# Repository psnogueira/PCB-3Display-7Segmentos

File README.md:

# PCB-3Display-7Segmentos
Projeto esquemático e PCB de um circuito controlado por Arduino de 3 displays de 7 segmentos de um contador de 0 a 999.

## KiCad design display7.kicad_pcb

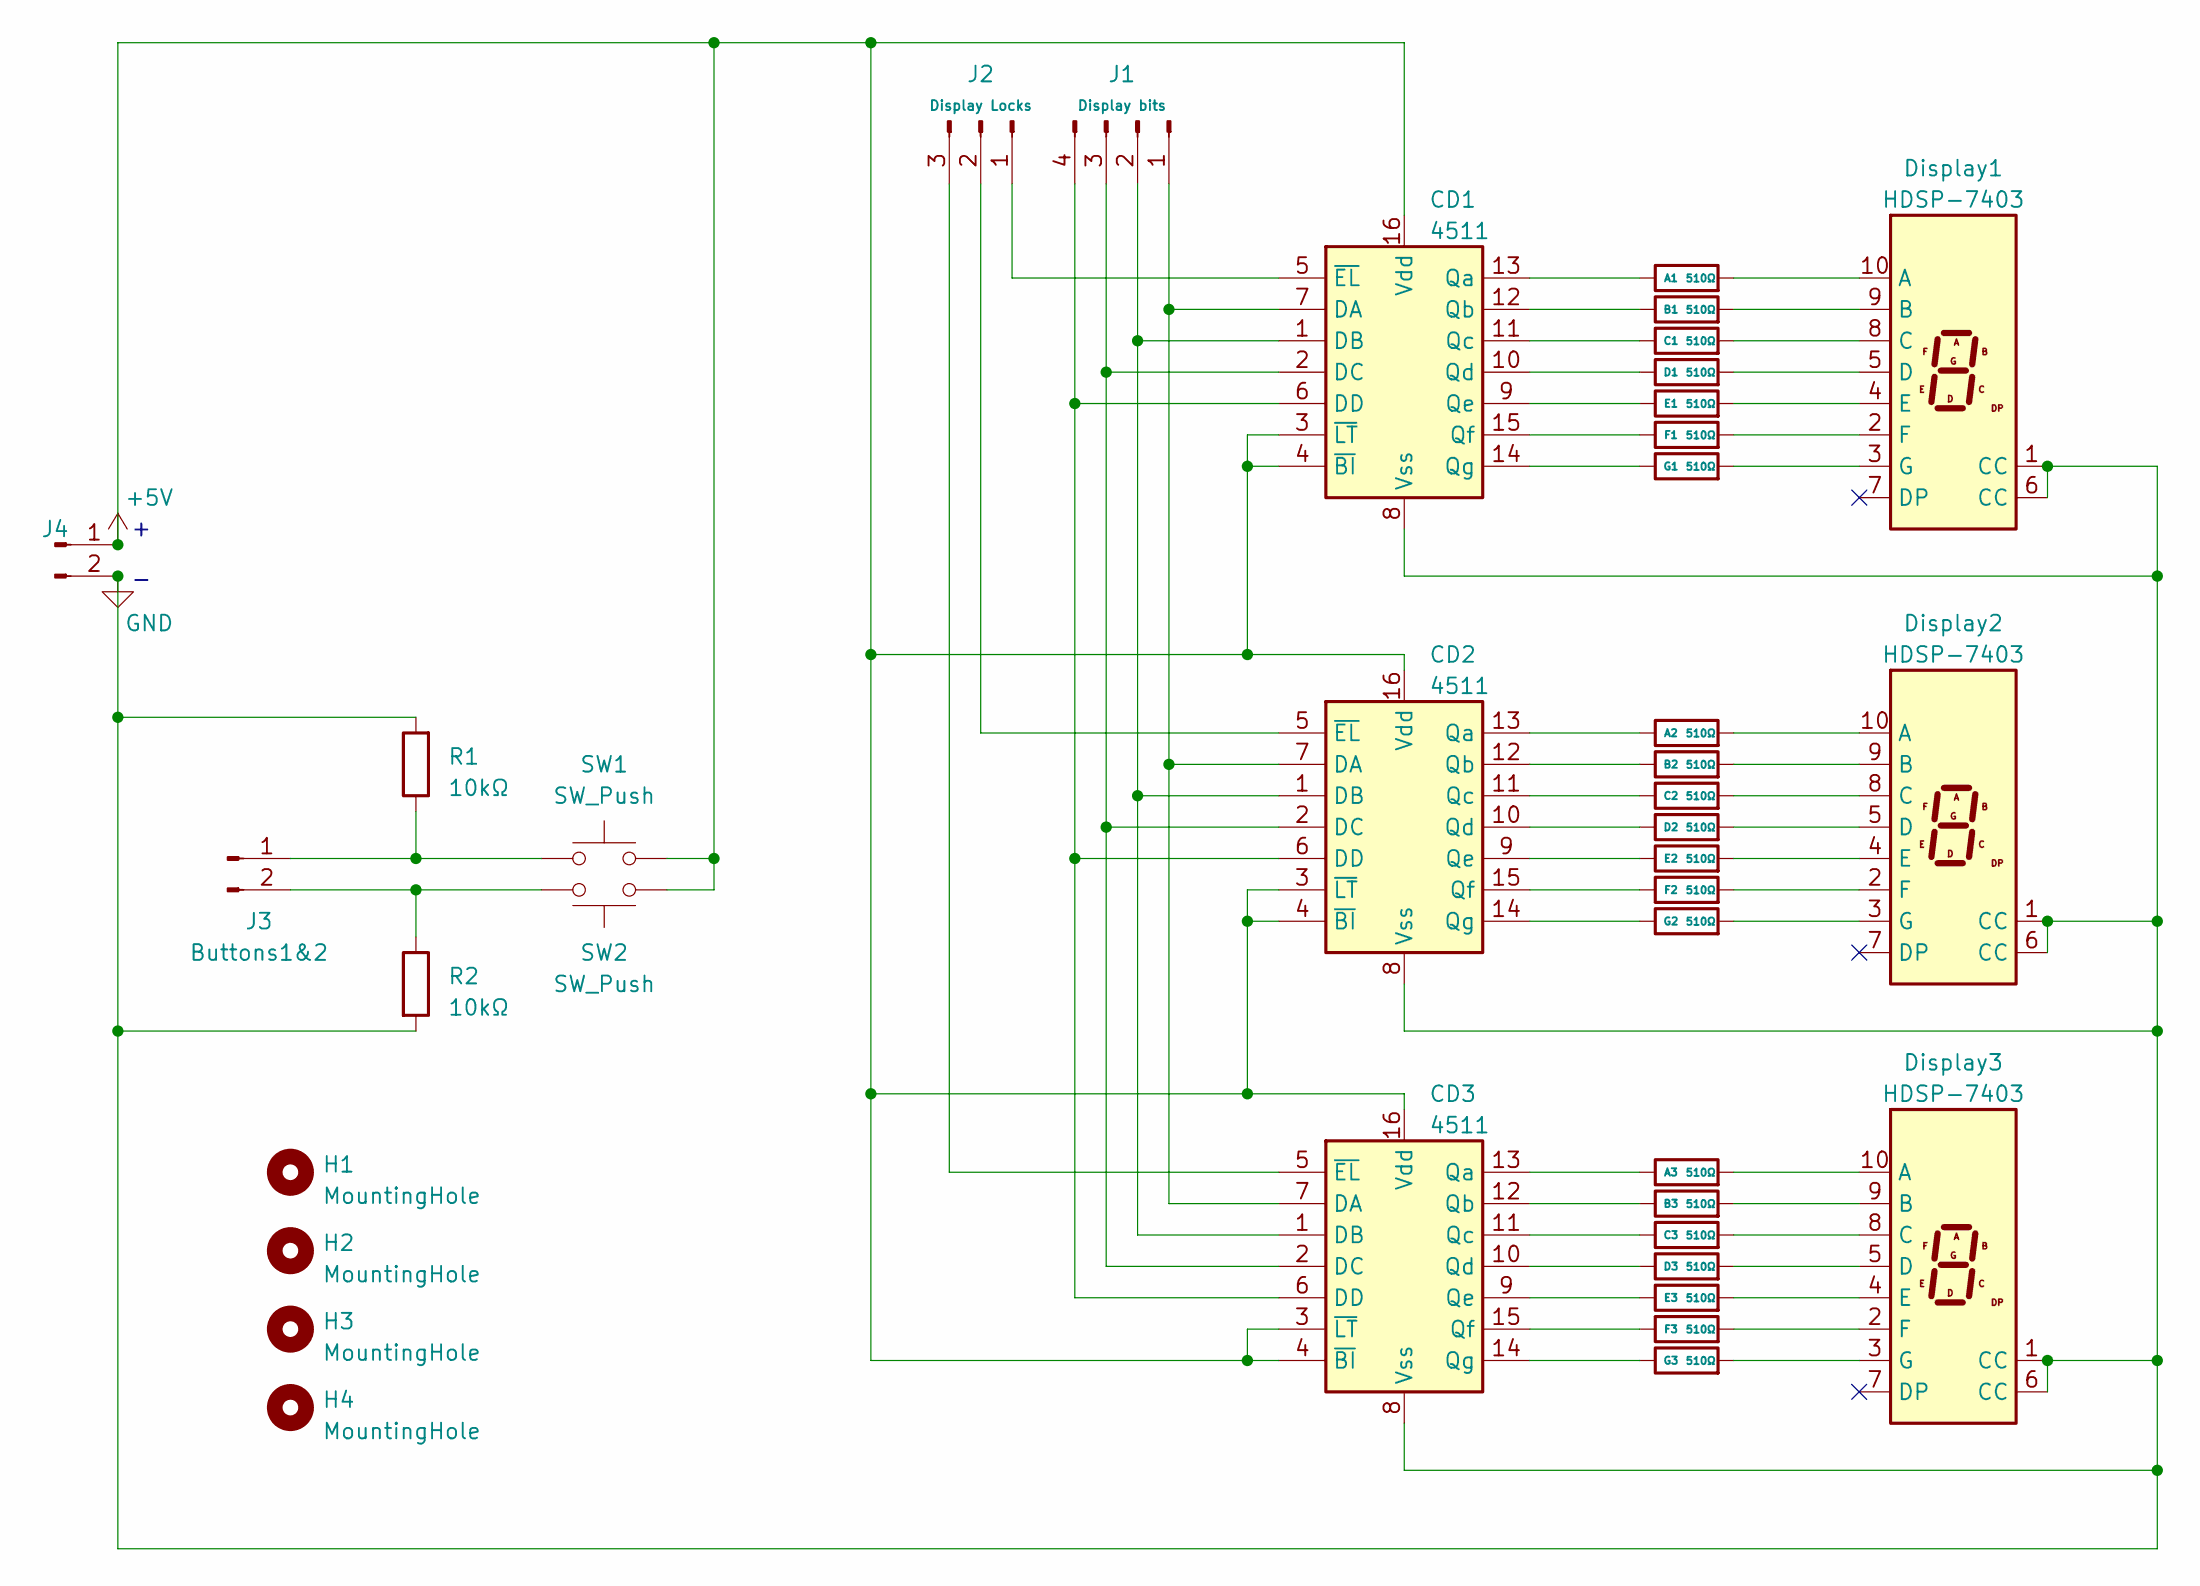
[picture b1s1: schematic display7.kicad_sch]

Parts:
A1, A2, A3: 510Ω; R_0402_1005Metric
B1, B2, B3: 510Ω; R_0402_1005Metric
C1, C2, C3: 510Ω; R_0402_1005Metric
CD1, CD2, CD3: 4511; DIP794W45P254L1969H508Q16
D1, D2, D3: 510Ω; R_0402_1005Metric
Display1, Display2, Display3: HDSP-7403; HDSP-7401
E1, E2, E3: 510Ω; R_0402_1005Metric
F1, F2, F3: 510Ω; R_0402_1005Metric
G1, G2, G3: 510Ω; R_0402_1005Metric
H1, H2, H3, H4: MountingHole; MountingHole_2.1mm
J1: Display bits; PinHeader_1x04_P2.54mm_Vertical
J2: Display Locks; PinHeader_1x03_P2.54mm_Vertical
J3: Buttons1&2; PinHeader_1x02_P2.54mm_Vertical
J4: PinHeader_1x02_P2.54mm_Vertical
R1, R2: 10kΩ; R_0402_1005Metric
SW1, SW2: SW_Push; SW_PUSH_6mm

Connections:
+5V: CD1.3 (~LT), CD1.4 (~BI), CD1.16 (Vdd), CD2.3 (~LT), CD2.4 (~BI), CD2.16 (Vdd), CD3.3 (~LT), CD3.4 (~BI), CD3.16 (Vdd), J4.1, SW1.2, SW2.1
GND: CD1.8 (Vss), CD2.8 (Vss), CD3.8 (Vss), Display1.1 (CC), Display1.6 (CC), Display2.1 (CC), Display2.6 (CC), Display3.1 (CC), Display3.6 (CC), J4.2, R1.2, R2.2
unnamed: CD1.7 (DA), CD2.7 (DA), CD3.7 (DA), J1.1
unnamed: CD1.1 (DB), CD2.1 (DB), CD3.1 (DB), J1.2
unnamed: CD1.2 (DC), CD2.2 (DC), CD3.2 (DC), J1.3
unnamed: CD1.6 (DD), CD2.6 (DD), CD3.6 (DD), J1.4
unnamed: A1.1, CD1.13 (Qa)
unnamed: B1.1, CD1.12 (Qb)
unnamed: C1.1, CD1.11 (Qc)
unnamed: CD1.10 (Qd), D1.1
unnamed: CD1.9 (Qe), E1.1
unnamed: CD1.15 (Qf), F1.1
unnamed: CD1.14 (Qg), G1.1
unnamed: CD1.5 (~EL), J2.1
unnamed: A2.1, CD2.13 (Qa)
unnamed: B2.1, CD2.12 (Qb)
unnamed: C2.1, CD2.11 (Qc)
unnamed: CD2.10 (Qd), D2.1
unnamed: CD2.9 (Qe), E2.1
unnamed: CD2.15 (Qf), F2.1
unnamed: CD2.14 (Qg), G2.1
unnamed: CD2.5 (~EL), J2.2
unnamed: A3.1, CD3.13 (Qa)
unnamed: B3.1, CD3.12 (Qb)
unnamed: C3.1, CD3.11 (Qc)
unnamed: CD3.10 (Qd), D3.1
unnamed: CD3.9 (Qe), E3.1
unnamed: CD3.15 (Qf), F3.1
unnamed: CD3.14 (Qg), G3.1
unnamed: CD3.5 (~EL), J2.3
unnamed: A1.2, Display1.10 (A)
unnamed: B1.2, Display1.9 (B)
unnamed: C1.2, Display1.8 (C)
unnamed: D1.2, Display1.5 (D)
unnamed: Display1.4 (E), E1.2
unnamed: Display1.2 (F), F1.2
unnamed: Display1.3 (G), G1.2
unnamed: A2.2, Display2.10 (A)
unnamed: B2.2, Display2.9 (B)
unnamed: C2.2, Display2.8 (C)
unnamed: D2.2, Display2.5 (D)
unnamed: Display2.4 (E), E2.2
unnamed: Display2.2 (F), F2.2
unnamed: Display2.3 (G), G2.2
unnamed: A3.2, Display3.10 (A)
unnamed: B3.2, Display3.9 (B)
unnamed: C3.2, Display3.8 (C)
unnamed: D3.2, Display3.5 (D)
unnamed: Display3.4 (E), E3.2
unnamed: Display3.2 (F), F3.2
unnamed: Display3.3 (G), G3.2
unnamed: J3.1, R1.1, SW1.1
unnamed: J3.2, R2.1, SW2.2

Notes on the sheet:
+ -

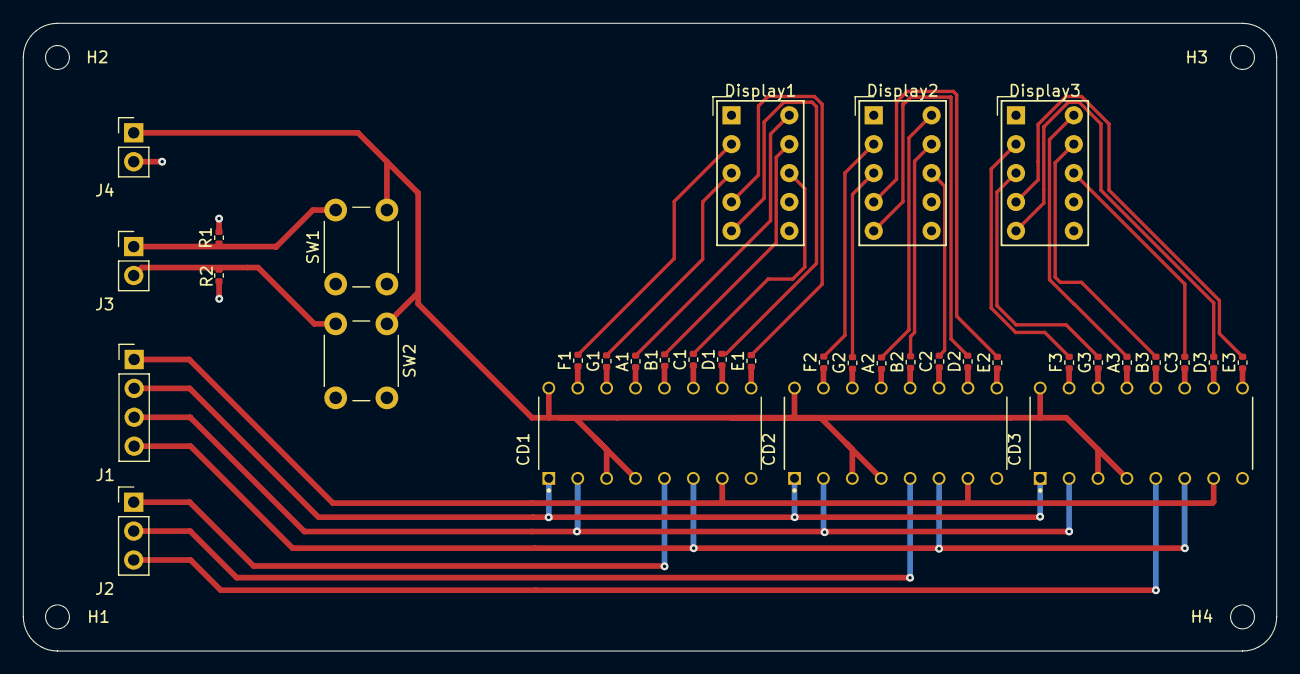
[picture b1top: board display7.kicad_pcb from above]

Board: 2 copper layers, 110.1 x 55.2 mm, 39 parts (0 on the bottom side), 53 nets.
